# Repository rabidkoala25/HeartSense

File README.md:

# HeartSense

a little magnetic field meter i made. it reads how strong the magnetic field
is around you and shows it on a screen with a scroll wheel to get through the
menu. 

my reason for making this device is because my friend wears a pacemaker, and was concerned of being in a highly magnetic environment. this device lets them see the ambient magnetic field strength, avoiding interference with their pacemaker. 

this repo has the hardware. the code is in its own repos:

- firmware: https://github.com/rabidkoala25/HeartSense-Firmware
- simulator: https://github.com/rabidkoala25/HeartSenseDemo
    - https://rabidkoala25.github.io/HeartSenseDemo/ 

## images

## hardware/

the KiCad files are in here. open `HeartMeter.kicad_pro`. the gerbers in
`gerbers/`, and `3d/`  the 3d models.

if you find anything that says HeartMeter, that's what it was called before i changed it to HeartSense

## soldering note

all components are through hole, save for the SMD charging chip which will be assembled not by me.

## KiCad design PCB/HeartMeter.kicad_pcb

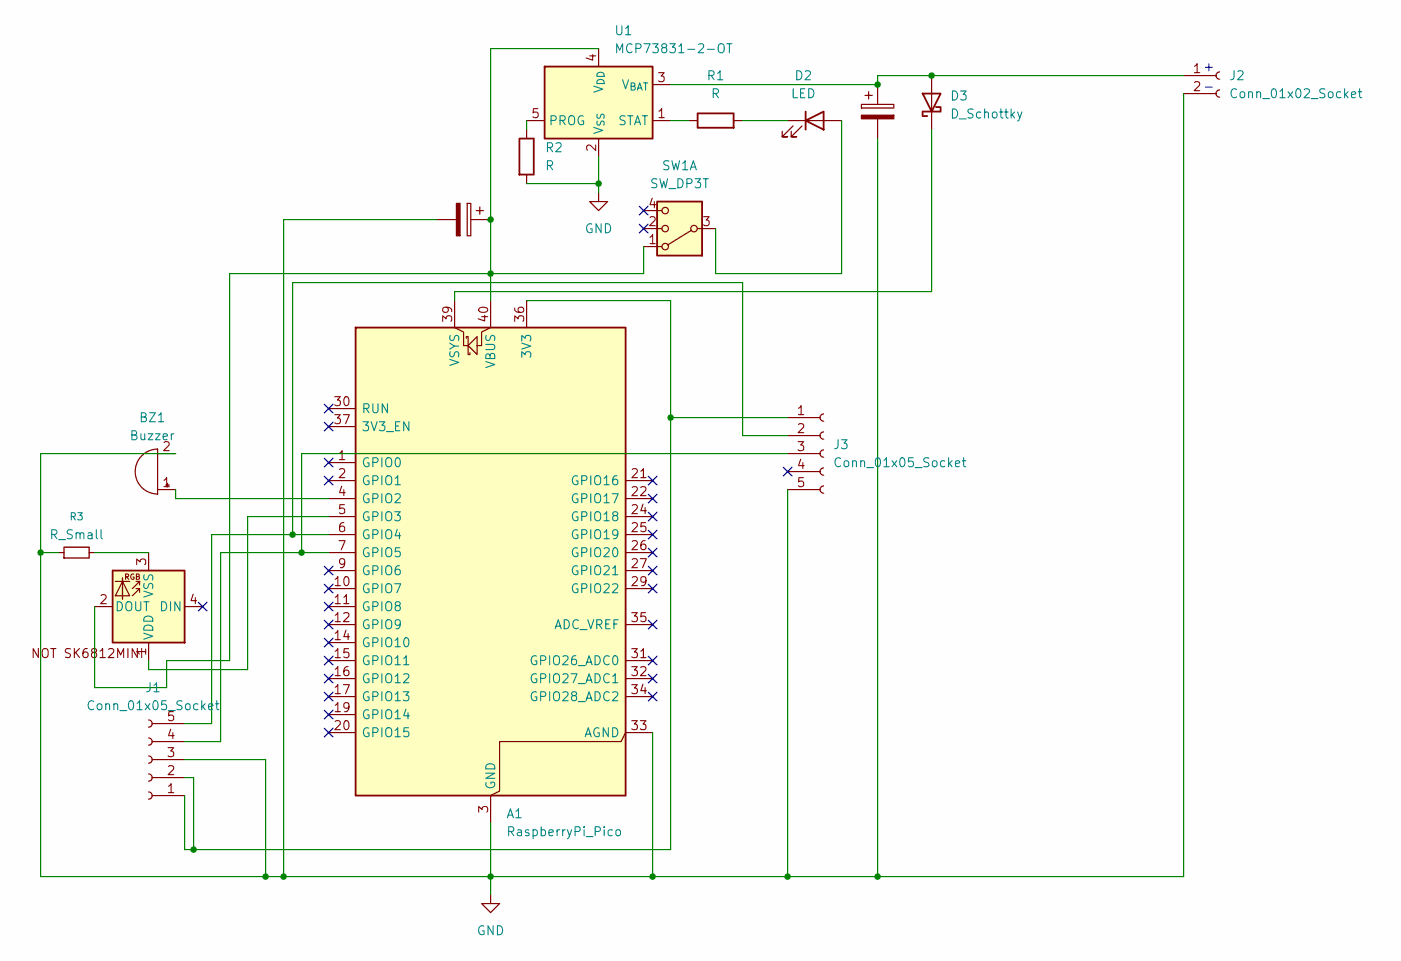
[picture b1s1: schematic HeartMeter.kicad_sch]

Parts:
A1: RaspberryPi_Pico; RaspberryPi_Pico_Common_THT
BZ1: Buzzer; Buzzer_TDK_PS1240P02BT_D12.2mm_H6.5mm
C3, C4: C_Polarized; CP_Radial_D5.0mm_P2.00mm
D1: SK6812MINI-E; LED_D5.0mm-4_RGB
D2: LED; LED_D3.0mm_Horizontal_O1.27mm_Z2.0mm
D3: D_Schottky; D_DO-41_SOD81_P7.62mm_Horizontal
J1: Conn_01x05_Socket; PinSocket_1x05_P2.54mm_Vertical
J2: Conn_01x02_Socket; PinSocket_1x02_P2.54mm_Horizontal
J3: Conn_01x05_Socket; POMORONI OLED i2C
R1, R2: R; R_Axial_DIN0207_L6.3mm_D2.5mm_P7.62mm_Horizontal
R3: R_Small; SolderWire-0.1sqmm_1x02_P3.6mm_D0.4mm_OD1mm
SW1: SW_DP3T; SW_CK_JS202011AQN_DPDT_Angled
U1: MCP73831-2-OT; SOT-23-5

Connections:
GND: A1.3 (GND), A1.8 (GND), A1.13 (GND), A1.18 (GND), A1.23 (GND), A1.28 (GND), A1.33 (AGND), A1.38 (GND), BZ1.2 (-), C3.2, C4.2, J1.3, J2.2, J3.5, R2.2, R3.1, U1.2 (V_{SS})
unnamed: A1.36 (3V3), J1.1, J1.2, J3.1
unnamed: A1.4 (GPIO2), BZ1.1 (+)
unnamed: A1.5 (GPIO3), D1.1 (VDD)
unnamed: A1.6 (GPIO4), J1.5, J3.2
unnamed: A1.7 (GPIO5), J1.4, J3.3
unnamed: A1.40 (VBUS), C4.1, D1.2 (DOUT), SW1.1, U1.4 (V_{DD})
unnamed: A1.39 (VSYS), D3.1 (K)
unnamed: D1.3 (VSS), R3.2
unnamed: D2.2 (A), SW1.3
unnamed: D2.1 (K), R1.2
unnamed: C3.1, D3.2 (A), J2.1, U1.3 (V_{BAT})
unnamed: R2.1, U1.5 (PROG)
unnamed: R1.1, U1.1 (STAT)

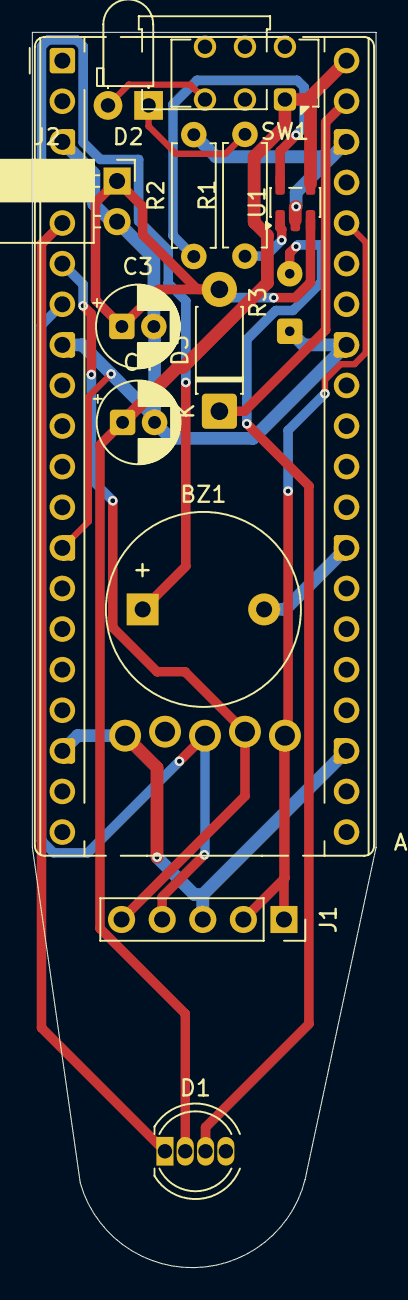
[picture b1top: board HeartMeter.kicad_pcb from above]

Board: 2 copper layers, 21.5 x 77.3 mm, 15 parts (1 on the bottom side), 14 nets.
